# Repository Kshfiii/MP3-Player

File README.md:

# MP3 Player

 A strawberry-shortcake themed MP3 player built around the DF player mini, and supported by the Xiao Esp32 C3. 

 ## About
 This is a fully self-contained MP3 Player with onboard LiPo charging, a boost-converted 5V motor supply, and a DFPlayer Mini for audio playback on a custom PCB. The xiao handles the pause/play logic via UART communication with the DF player, it was also used because of the in-built BMS and direct charging support.

### Schematics

### PCB 

### CAD
[Onshape file](https://cad.onshape.com/documents/b89701995e34a629cb20daf8/w/a087d5ccfa9ba9747f812881/e/695f8d85722ae4ab0145bd85)

## Assembly
Put the components into their respective spots in the PCB. Put the circular parts into the two holes and then put in the speakers. Add tactile switches to the square placeholder and put the pink buttons on them. Now, add brass inserts onto the back of the Mp3 player and fix the back with screws. 

## Usage & Features

  1. Charge via the USB-C port on the XIAO ESP32-C3
  2. Power on using the slide switch
  3. short press left button for previous song, long press to increase volume
  4. short press right button for next song, long press to decrease volume
  5. Press middle button to pause/play

## Note
1. Attach lipo batter to GND and BATT+ pins on the underside of the Esp32. 
2. Upload audio files to sd card in format, 
   <pre> SD_CARD/
     ├── 0001.mp3
     ├── 0002.mp3
     ├── 0003.mp3
     └── 0004.mp3
   </pre>

## Component List

  1. Seeed Studio XIAO ESP32-C3
  2. DFPlayer Mini (YX5200)
  3. MT3608 Boost Converter IC
  4. AMS1117-5.0 LDO Regulator
  5. 8Ω 1W Speaker
  6. Tactile Switch
  7. 3.7V LiPo Battery

## Bill of Materials
| Component | Quantity | Est. Cost (USD) | Purchase Links | 
| :--- | :---: | :--- | :--- | 
| **Seeed Studio XIAO ESP32-C**| 1 | $11.50 |[Link](https://www.aliexpress.com/item/1005009855437801.html?spm=a2g0o.detail.0.0.378eYyHPYyHPz5&mp=1&pdp_npi=6%40dis%21USD%21USD%2011.43%21USD%2010.93%21%21USD%2010.93%21%21%21%40212e508f17759555552744763e9213%2112000050381761106%21ct%21PK%21-1%21%211%210%21) | 
| **DFPlayer Mini** | 1 | $5.50 | [Link](https://www.aliexpress.com/item/1005011540339952.html?spm=a2g0o.detail.0.0.4b1akxSAkxSANK&mp=1&pdp_npi=6%40dis%21USD%21USD%205.19%21USD%201.99%21%21USD%201.99%21%21%21%40212e520d17760065522677760e7f39%2112000055866842276%21ct%21PK%21-1%21%211%210%21)| 
| **MT3608 Boost Converter IC** | 1 | $1.20 | [Link](https://www.aliexpress.com/item/1005008853748359.html?spm=a2g0o.detail.0.0.378eYyHPYyHPz5&mp=1&pdp_npi=6%40dis%21USD%21USD%202.73%21USD%202.23%21%21USD%202.23%21%21%21%40212e508f17759555552744763e9213%2112000046953414150%21ct%21PK%21-1%21%211%210%21) | 
| **AMS1117-5.0 LDO Regulator** | 1 | $2.50 | [Link](https://www.aliexpress.com/item/1005002487704059.html?spm=a2g0o.productlist.main.4.2196rhF6rhF6yu&aem_p4p_detail=20260411180108338023986275640001084750&algo_pvid=16ee6a6a-aaf1-43e2-94e3-907dfa61e2f0&algo_exp_id=16ee6a6a-aaf1-43e2-94e3-907dfa61e2f0-3&pdp_ext_f=%7B%22order%22%3A%223440%22%2C%22eval%22%3A%221%22%2C%22fromPage%22%3A%22search%22%7D&pdp_npi=6%40dis%21USD%212.59%212.09%21%21%212.59%212.09%21%402151e6dc17759556679336660e6cfb%2112000020837902169%21sea%21PK%210%21ABX%211%210%21n_tag%3A-29910%3Bd%3A12fde4ed%3Bm03_new_user%3A-29895%3BpisId%3A5000000203713833&curPageLogUid=jNloBkgONfbe&utparam-url=scene%3Asearch%7Cquery_from%3A%7Cx_object_id%3A1005002487704059%7C_p_origin_prod%3A&search_p4p_id=20260411180108338023986275640001084750_1) | 
| **8Ω 1W Speaker** | 1 | $1.70 | [Link](https://www.aliexpress.com/item/1005008660223571.html?spm=a2g0o.detail.0.0.173cVO5QVO5QJV&mp=1&pdp_npi=6%40dis%21USD%21USD%204.39%21USD%201.70%21%21USD%201.70%21%21%21%402151e6dc17759543473957645e6ce1%2112000046135720888%21ct%21PK%21-1%21%211%210%21) | 
| **Tactile Switch** | 3 | $1.50 | [Link](https://digilog.pk/products/12-x-12mm-x-7-5mm-push-button-in-pakistan-en?variant=44490991370518 )| 
| **PCB** | 1 | $6.00 | [Link](https://jlcpcb.com/)| 
| **Total Build Cost:** |  | **~$30.00** |

#
Happy Building :)

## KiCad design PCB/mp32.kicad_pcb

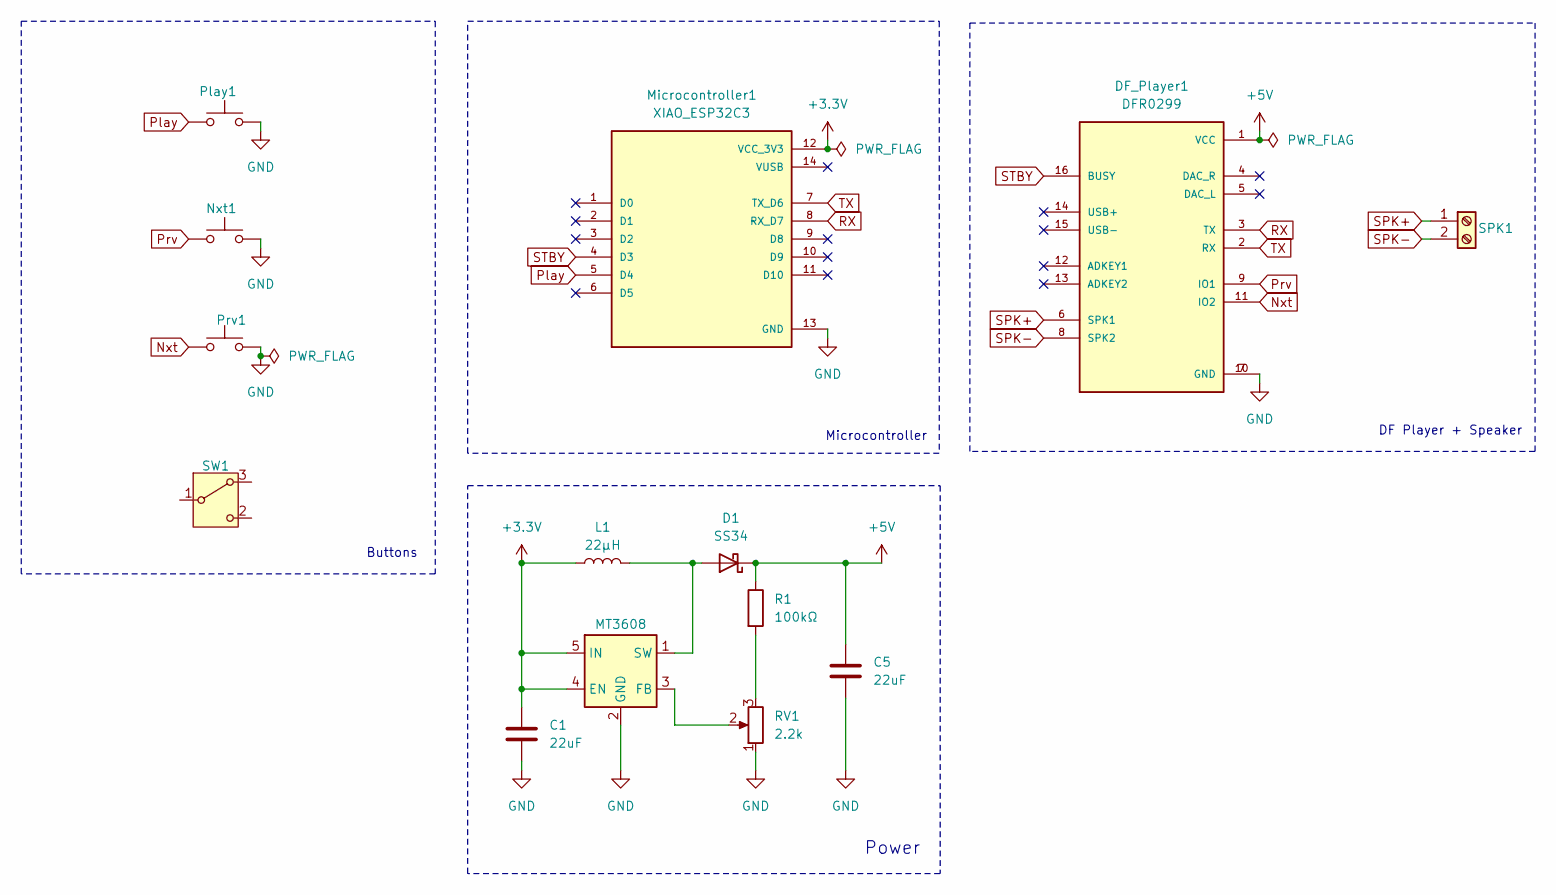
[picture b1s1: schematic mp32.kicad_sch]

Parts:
C1, C5: 22uF; C_0805_2012Metric_Pad1.18x1.45mm_HandSolder
D1: SS34; D_SMA_Handsoldering
DF_Player1: DFR0299; MODULE_DFR0299
L1: 22µH; L_APV_APH0420
Microcontroller1: XIAO_ESP32C3; MODULE_XIAO_ESP32C3; PARTREV 23/05/2022
Nxt1: SW_Push; SW_PUSH_6mm_H8mm
Play1: SW_Push; SW_PUSH_6mm_H8mm
Prv1: SW_Push; SW_PUSH_6mm_H8mm
R1: 100kΩ; R_0805_2012Metric
RV1: 2.2k; Potentiometer_ACP_CA6-VSMD_Vertical_Hole
SPK1: SPK; TerminalBlock_Xinya_XY308-2.54-2P_1x02_P2.54mm_Horizontal
SW1: SW_Wuerth_450301014042; SW_Slide-03_Wuerth-WS-SLTV_10x2.5x6.4_P2.54mm
U6: MT3608; SOT-23-6

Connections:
+3.3V: C1.2, L1.1, Microcontroller1.12 (VCC_3V3), U6.4 (EN), U6.5 (IN)
+5V: C5.2, D1.1 (K), DF_Player1.1 (VCC), R1.1
GND: C1.1, C5.1, DF_Player1.7 (GND), DF_Player1.10 (GND), Microcontroller1.13 (GND), Nxt1.2, Play1.2, Prv1.2, RV1.1, U6.2 (GND)
unnamed: D1.2 (A), L1.2, U6.1 (SW)
unnamed: R1.2, RV1.3
unnamed: RV1.2, U6.3 (FB)
Nxt: DF_Player1.11 (IO2), Prv1.1
Play: Microcontroller1.5 (D4), Play1.1
Prv: DF_Player1.9 (IO1), Nxt1.1
RX: DF_Player1.3 (TX), Microcontroller1.8 (RX_D7)
SPK+: DF_Player1.6 (SPK1), SPK1.1
SPK-: DF_Player1.8 (SPK2), SPK1.2
STBY: DF_Player1.16 (BUSY), Microcontroller1.4 (D3)
TX: DF_Player1.2 (RX), Microcontroller1.7 (TX_D6)

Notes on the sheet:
DF Player + Speaker
Microcontroller
Buttons
Power

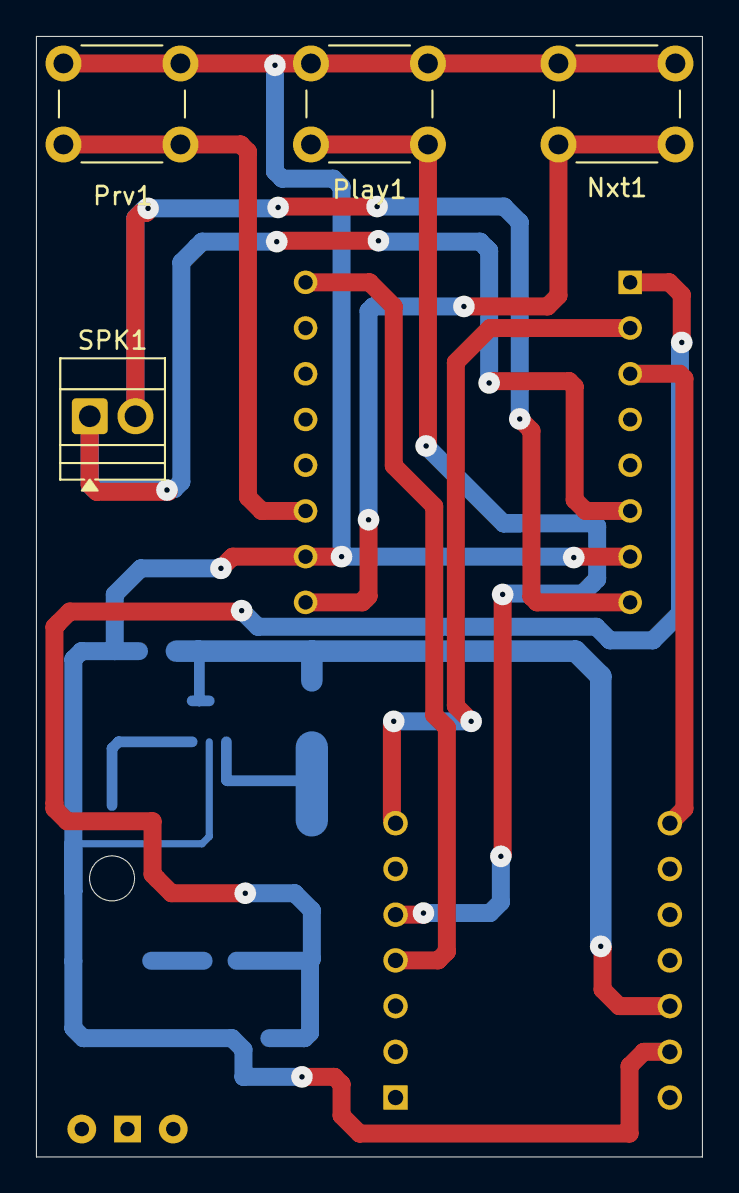
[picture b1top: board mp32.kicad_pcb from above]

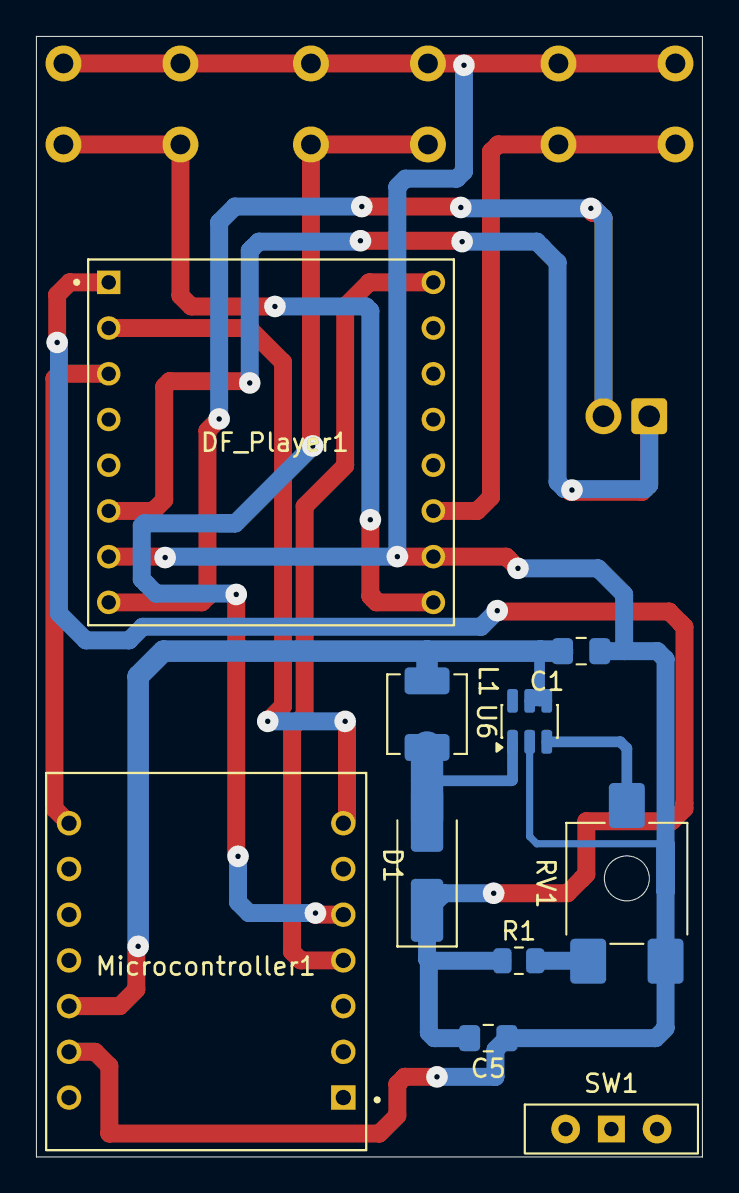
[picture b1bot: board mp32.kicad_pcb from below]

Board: 2 copper layers, 37.0 x 62.3 mm, 14 parts (10 on the bottom side), 14 nets.

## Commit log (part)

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2026-06-01 Create LICENSE
2026-06-01 Add title for MP3 Player project in README
